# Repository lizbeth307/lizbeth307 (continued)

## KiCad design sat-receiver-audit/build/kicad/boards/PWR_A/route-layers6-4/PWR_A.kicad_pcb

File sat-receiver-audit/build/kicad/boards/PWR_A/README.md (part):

# PWR-A: розміщення і пробне розведення (W2 PCB-PWRA-1, PCB-PWRA-2, PCB-PWRA-3, PCB-PWRA-4)

**Статус: MODEL, NOT FOR FABRICATION.** Тут немає плати PWR-A, розведення чи файлів виробництва. Є специфікація-планувальник двобічної PWR-A SHRINK-2 з усіма 280 позиціями, заякореними силовими каскадами і скриптовою міддю (частина 2 W2 PCB-PWRA-3), розрахунок розміщення і пробні плати з прогонів CI: плата-скелет чернетки у `skeleton-probe/` (24 якорі графа, заглушка стику B2B2 і скриптова мідь, проба 4) і проба розміщення SHRINK-2 у `placement-probe/` (235 позицій у стані `pending`, проба 7). Це записи; вони відповідають графу до GR-5A. Результати нижче — розрахунок планувальника `pcb/board_gen.py` на стандартній бібліотеці та вимір CI на пробних платах. Вони не є результатом CI-збірки плати й не є апаратним PASS. Усі стендові ворота (тепловий контакт, струм і нагрів, бюджет опору E1-05) лишаються OPEN.

**Стан лінії після рішення про площу (11.11.2026).** F2 піднято вимірюванням: у W2 PCB-PWRA-1 заповнення всіма позиціями 0.959, планувальник розмістив 160 з 256 позицій, а варіанти F2a, F2b і обидва разом дали 0.783, 0.915 і 0.740 проти порога 0.60 (розділ «Результат»). Відповідь на F2 — SHRINK-2 (рядки W2 AREA-2 у build/15). Корпус і пара PWR-A/PWR-B на стику Samtec LSHM-150 лишаються. PWR-A звільняє місце меншим вмістом: SMD-перетворювачі TI замість модулів Pololu, SMD-запобіжники F103/F201, нижчі демпфери й дроселі, другий бік плати, правило H-TRIM і злиті роз'єми PWR-B. Цю лінію продовжують W2 PCB-PWRA-3 (виправлення `placement_study.py`, двобічна специфікація, скриптова мідь) і W2 PCB-PWRA-4 (розведення до DRC 0 і набір виробництва). Частина 1 W2 PCB-PWRA-3 (12.11.2026) виправила `placement_study.py`, перерахувала чернетку і перенесла будівник SHRINK-2 у `make_spec.py`; розрахунок і проби — розділи «Двобічна PWR-A SHRINK-2» і «Проба розміщення». Частина 2 (12.11.2026, після злиття GR-5A, GR-5B і MECH-7 у wip/w2-shrink d45870ca) перегенерувала специфікацію на реальних деталях, заякорила силові каскади й додала скриптову мідь — розділ «Частина 2: реальні деталі, силові каскади, скриптова мідь». Мету W2 PCB-PWRA-2 (розведення всіх позицій до DRC 0, перевірка THT і B2B на повній платі, набір виробництва) SHRINK-2 замінив. Пакет закрито пробами 2–4 (розділ «Пробна плата-скелет»), без нового розміщення чи розведення.

**Стан після W2 PCB-PWRA-4 (12.11.2026): F2-C спрацював.** Плату SHRINK-2 з усіма 280 позиціями дві ітерації розміщення розводили в CI (`sr-rx-pcb`, KiCad 10.0.7, Freerouting 2.5.0). Ітерація 1 лишила 220 нез'єднань і 70 помилок DRC, ітерація 2 — 198 нез'єднань і 11 помилок; кола лишилися нерозведеними після двох ітерацій розміщення, тож за брифом і тригером F2-C рішення SHRINK-2 пакет зупинився й підняв F2-C з числами (розділ «Розведення W2 PCB-PWRA-4»). Плати запису, набору виробництва і `pcb/boards/PWR_A.json` немає; виходи обох прогонів лежать як записи в `route-iteration-1/` і `route-iteration-2/`. Усе — CI/MODEL, не апаратний PASS; стендові ворота лишаються OPEN.

## Файли

| Файл | Що це |
|---|---|
| `PWR_A.spec-draft.json` | Чернетка специфікації плати за схемою `srrx-board-spec-v1`. Містить усі 256 позицій доменів PWR_MAIN, PWR_BRANCH і USB_POWER (`pcb/generated/partition.json`), тотожну мапу позицій і кіл, 4 шари, якорі, групи розміщення, таблицю вільних прямокутників `regions`, резерв під B2B, скриптову мідь, заливки після розведення та політику DRC. |
| `PWR_A.kicad_pro` | Проєкт KiCad 10.0.7: переглянуті рівні серйозності DRC (як в ENC) і класи кіл із `pcb/generated/netclasses.json`. Default/SIG має 0.15 мм, PWR1A — 0.35, PWR2A — 0.8, PWR3A — 1.85, BATT — 3.2 мм; зазор усіх класів 0.15 мм, переходи 0.6/0.3 мм. Шаблони кіл узято з `netclasses.json`, лише 48 кіл цієї плати. Мінімальний наскрізний отвір — 0.2 мм, бо футпринт LT3045 з бібліотеки KiCad (MSOP-12-1EP ThermalVias) свердлить 0.2 мм; підлога JLC для 4 шарів — 0.15 мм. |
| `placement_study.py` | Розрахунок, лише стандартна бібліотека. Він бере з `pcb/board_gen.py` перевірку специфікації, розв'язання кіл, геометрію футпринтів і полицевий пакувальник; нічого з цього не переписано. Рахує специфікацію SHRINK-2 (`SPECS`) → `placement-study-shrink2.json`; режим `--check` перевіряє відтворення. З W2 PCB-PWRA-3: виправлення перешкод, групи нижнього боку, заплановані футпринти, перевірка b2b з графовим партнером J209, H-TRIM, незалежна перевірка перекриттів `placement_checks`. Частина 2 додала: перевірку курт'ярдів низу в кишенях PB1–PB13, зон перетворювачів (`converter_zones`), кінця нижнього ряду роз'ємів (`bottom_row`), наскрізні переходи як перешкоди низу, вільну смугу праворуч від частини групи (`<область>>`), зону-заборону скриптової міді (вид `copper`, не попит площі) і перевірку скриптової міді (ширини, площадки, зазори між заливками, переходи). Виправлення огляду (F1/F2): перевірка магістралей (`scripted_copper_precheck.trunks`: скриптова мідь кожного силового кола сама з'єднує свої площадки), заливки на внутрішньому шарі (In2) і звіт коридорів (`corridor_precheck`, растр 0.2 мм: чи досягає мідь ширини класу F.Cu/B.Cu площадок, які лишено роутеру). |
| `placement-study.json` | Застиглий запис (частина 1): розрахунок чернетки з виправленням перешкод на графі wip/w2-shrink 59c68774 (166 з 257). Після GR-5A чернетка з графом не розв'язується (U107/U108 — перетворювачі TI, C107.1 — E1_CONV_IN), тож `--check` її не перевіряє; `--spec PWR_A.spec-draft.json` рахує її лише на дереві до GR-5A. |
| `placement-study-shrink2.json` | Згенерований результат (§2): не редагувати вручну, а перезапустити `python3 build/kicad/boards/PWR_A/placement_study.py`. |
| `make_spec.py` | Генератор специфікації SHRINK-2 (W2 PCB-PWRA-3, стандартна бібліотека), перенесений у репозиторій скретч-будівник рішення SHRINK-2. Читає чернетку, граф, `pcb/partition-spec.json` candidates.shrink2, стан запланованих змін (з частини 2 — наживо за правилом `pcb/partition_budget.py` Evaluator.planned, бо `pcb/partition-budget.json` старший за граф до AREA-2b), J209 з `pcb/boards/PWR_B.json`, карту контактів `pcb/generated/b2b-nets.json` і контракт MECH-7 (зони 3'/4', кишені PB1–PB13, `row_end_max`); дизайн не змінює. Пише `PWR_A.spec-shrink2.json`; `--check` перевіряє відтворення. |
| `PWR_A.spec-shrink2.json` | Згенерована (§2) специфікація-планувальник двобічної PWR-A SHRINK-2: 280 позицій, 48 якорів (силові каскади з вузлами SYS12 і LAB5, роз'єми, J208, регулятори зон 1–2), групи верху й низу, області `regions.rects` і `regions.bottom_rects` (кишені), скриптова мідь `pre_route` (55 зон: 46 на F.Cu, 4 на B.Cu, 3 на In2.Cu і 2 площини GND In1/In2; 64 переходи, 1 доріжка). Лежить тут, а не в `pcb/boards/`: плату запису (розведення до DRC 0, набір виробництва) робить W2 PCB-PWRA-4. |
| `make_probe_spec.py` | Генератор специфікацій проб (стандартна бібліотека). Скелет SHRINK-2 (частина 2): позиції з якорями (силові каскади, роз'єми, J208, регулятори зон 1–2), уся скриптова мідь (зони, переходи, доріжка), заливки після розведення, яких досягає площадка або перехід їхнього кола, і запропоновані кишені пластини для кожного скупчення THT-площадок → `skeleton-probe-shrink2/probe-spec.json`. Проба розміщення з `PWR_A.spec-shrink2.json` і `placement-study-shrink2.json`: кожна розміщена позиція на своєму місці, боці й куті → `placement-probe-shrink2/probe-spec.json`. `--install skeleton\|placement` копіює вибрану в `pcb/boards/PWR_A.json` лише для коміту проби; `--check` перевіряє обидві. Скелет чернетки (`skeleton-probe/`) — застиглий запис, `--draft-skeleton` будує його лише на дереві до GR-5A. |
| `lab5_budget.py`, `lab5-budget.json` | Модель опору міді LAB5 E1→E2 проти E1-05 (≤10 мОм; CC-36 п. 12), стандартна бібліотека. З W2 PCB-PWRA-3 бере якорі `PWR_A.spec-shrink2.json` і пару стику J208/J209 (LSHM-150); з частини 2 кінець E1 — L101.2, а скриптові заливки E1_LAB5_RAW і E1_LAB5_FUSED дають верхню межу міді перед E1-05. `lab5-budget.json` згенеровано (§2): MODEL з геометрії, не вимір. |
| `skeleton-probe/` | Застиглий запис: вихід прогону маршрутизації в CI для проби 4 чернетки (run 42424937979): 24 якорі графа, заглушка B2B2 і скриптова мідь, плюс локальний огляд `check_boards`. Згенеровано, не редагувати; див. розділ нижче. |
| `placement-probe/` | Застиглий запис: вихід прогону маршрутизації в CI для проби 7 (частина 1, стан `pending`) з її специфікацією і локальний огляд `check_boards`. Згенеровано, не редагувати; див. розділ «Проба розміщення». |
| `skeleton-probe-shrink2/`, `placement-probe-shrink2/` | Згенеровані (§2) специфікації проб частини 2 (`probe-spec.json`): скелет SHRINK-2 (48 якорів і вся скриптова мідь) і повна проба розміщення (280 позицій). Прогону CI ще не було: див. «Проби частини 2 у CI». |
| `make_board.py` | Генератор специфікації плати для розведення (W2 PCB-PWRA-4, стандартна бібліотека): будує пробу розміщення PCB-PWRA-3 (усі 280 позицій на місцях), бере позиції `board-placement.json`, переводить скриптові заливки F.Cu/B.Cu у заблоковані доріжки зі стиками (`board_copper`) і перевіряє, що мідь кожного кола — один шматок, ставить перехід GND до площин біля кожної SMD-площадки GND (`gnd_fanout`, порт PWR_B), пише висоти й зони висот (вікна PWR-B, H-TRIM), `neck_exempt` для стрижнів на виводах, класи проєкту (SCRIPTED_GND, переходи 0.7/0.3). Пише `board-spec.json` і `PWR_A.kicad_pro`; `--install` копіює специфікацію в `pcb/boards/PWR_A.json` для коміту прогону; `--check`. |
| `board-spec.json` | Згенерована (§2) специфікація плати: стан генератора після ітерації 2 (виправлення ще не розведено). |
| `place_board.py`, `board-placement.json` | Перерозміщення з урахуванням кіл (W2 PCB-PWRA-4, стандартна бібліотека): 201 позиція, що не є якорем специфікації SHRINK-2 і не має вирізу PWR-B, переходить на законні місця (контур, отвори, скриптова мідь і переходи, переходи GND нерухомих деталей, зони H-TRIM для деталей вищих за 2.7 мм, кишені пластини для нижніх чіпів), далі відпал із фіксованим зерном за половиною периметра кіл без GND із вагою класу. `board-placement.json` згенеровано (§2); `--check`. |
| `board_audit.py`, `board-audit.json` | Аудити PWR-A, яких немає в `check_boards` (W2 PCB-PWRA-4, стандартна бібліотека): зони 1–2 і 3'/4', нижні курт'ярди в кишенях PB1–PB13, H-TRIM, отвори без кола, кола E1_CELL0/B-, модель міді LAB5, E1_LAB5_RAW і E1_LAB5_FUSED, заповнення. Без плати в теці рахує заплановану плату `board-spec.json`; з `--dir` теки запису — розведену, а `--review` пише туди `review.json` `check_boards`. |
| `route-iteration-1/`, `route-iteration-2/` | Записи двох прогонів розведення W2 PCB-PWRA-4 (згенеровано, не редагувати): плата, `report.json`, `drc.json`, `connectors.json`, `route-log.json` з артефакту pcb-regenerated-PWR_A, `board-spec.json` (специфікація прогону), `review.json` і `board-audit.json` (локально). |
| `freeze/`, `route-frozen-6l.json` | Заморожене розведення 6-шарової проби W2 PWRJ-LAYERS6: копії інструментів PWR_B (`model.py`, `router.py`, `fin.py` з додатками `connect_all`, `neck_link`, `branch_pass`) і драйвер `freeze6.py` (numpy, офлайн, CI його не запускає); `route-frozen-6l.json` — мідь прогону 43349395168 (храповик 43339007739) з добудовою, шийками й гілками; `make_board.py` бере її лише при збігу захисту. |
| `route-layers6-3/` | Запис прогону 43354942122 проби W2 PWRJ-LAYERS6 (згенеровано, не редагувати): плата, `report.json`, `drc.json`, `connectors.json`, `route-log.json`, специфікація прогону, локальні `review.json` і `board-audit.json`. |

Специфікація навмисно лежить тут, а не в `pcb/boards/PWR_A.json`: специфікація в `pcb/boards/` без розведеної плати, що проходить перевірку, зробила б `sr-rx-pcb` червоним для всієї лінії інтеграції. Чернетка лишається записом до SHRINK-2. Специфікація SHRINK-2 з частини 2 має всі позиції домену (аудит домену пройдено, 280 позицій) і стає входом W2 PCB-PWRA-4, яка розводить плату запису і переносить її в `pcb/boards/PWR_A.json`. W2 PCB-PWRA-4 тримає так само і специфікацію плати: `make_board.py` пише `board-spec.json`, а в `pcb/boards/PWR_A.json` вона стоїть лише на коміт прогону (`--install`) або коли плата пройде.

## Шість шарів і 2 oz зовні (W2 PWRJ-LAYERS6, проба, CI/MODEL)

**Стан проби (13.11.2026, гілка wip/w2-pwrj-layers6): DRC 3 помилки, 64 нез'єднання, `ignored_checks` [] (sr-rx-pcb 43354942122).** Це вимір CI, не апаратний PASS; стендові ворота лишаються OPEN. Розміщення SHRINK-2 і оболонка не змінені: проба дає обом силовим платам 6 шарів.

**Шари.** S-G-S-S-P-S за таблицею JLC06161H-2116 (як PWR_B і 6-шаровий CTRL), замовлення з готовою міддю 2 oz зовні і 0.5 oz усередині (`pcb/generated/stackup-6l.json` `copper_options.outer_2oz`; jlcpcb.com/impedance, capabilities/pcb-capabilities і 6-layer-pcb прочитано 13.11.2026). In1.Cu — суцільна GND; In2.Cu і In3.Cu — лише сигнали; In4.Cu — заливка GND зі скриптовими заливками E1_CONV_IN (роль L3 4-шарового плану). Силові класи йдуть тільки по F.Cu/B.Cu (`router.class_layers`) і мають ширини для 2 oz за тим самим правилом IPC-2221 (MODEL): PWR1A 0.2, PWR2A 0.4, PWR3A 0.95, BATT 1.6 мм. Підлога JLC для 2 oz — 0.15/0.15 мм, рівно правило проєкту 0.15/0.15, тож запасу над підлогою зовні немає.

**Інструменти.** `freeze/` — копії `model.py`, `router.py`, `fin.py` з PWR_B і драйвер `freeze6.py`: заморожена мідь прогону плюс добудова сіткою A*. Добавки цієї проби: з'єднання пара за парою (`connect_all`), короткі шийки на виводах до 3 мм (`neck_link`, записуються в `neck_exempt`) і малострумові гілки до тестових точок, конденсаторів і резисторів від 100 Ом (`branch_pass`, 0.25/0.4 мм до 12 мм, записуються в `branch_exempt`); `--prev` збирає заморожену мідь попереднього файлу ще раз (храповик). `make_board.py` бере `route-frozen-6l.json` лише при збігу захисту (SHA256 площадок і скриптової міді). Режим FREEZE_ONLY вимикає автороутинг для прогону з замороженою міддю.

| Прогін | Що | DRC помилок | Нез'єднань |
|---|---|---|---|
| 43287918183 / 43295500516 | 4 шари, 1 oz (W2 PCB-PWRA-4) | 70 / 11 | 220 / 198 |
| 43339007739 | 6 шарів, 2 oz, Freerouting з нуля (222 → 191 нерозведених за його лічильником) | 1 | 138 |
| 43349395168 | заморожена мідь 43339007739 + добудова A* (10 шийок, 8 гілок), далі Freerouting | 9 | 64 |
| 43354942122 | храповик 43349395168 без 4 конфліктних шматків, автороутинг вимкнено | 3 | 64 |

Запис останнього прогону — `route-layers6-3/` (плата, звіт, DRC, журнал, специфікація прогону, локальні `review.json` і `board-audit.json`). `check_boards`: 0 знахідок (class_widths 0 на 2559 шматках, heights 0), 168 неперевірених (112 висот нижніх чіпів і роз'ємів, 35 гілок і шийок, 21 геометрія). `board_audit.py`: NO_FINDINGS, H-TRIM пройдено, бо J201 PWR-B стоїть у колонці між C219 і L102 (розміщення wip/w2-pwrbr-place). Три помилки DRC: перехід E2_AUX_SWITCHED замороженої міді на 0.1-мм стрижні LAB5, який board_gen щоразу додає до центру скриптового переходу (`via_centre_stubs`); `connection_width` на J208.1 (3V3_Q6A); 0.13-мм відгалуження E2_BONI_EF без з'єднання. Усі три — дефекти зібраної міді, не ємності.

**Чому не сходиться (MODEL, растр 0.1 мм на платі 43339007739).** Із 138 нез'єднань 104 — силові класи. Частка плати, де вміщається центр доріжки 1.6 мм (BATT), — 0.23 на F.Cu і 0.49 на B.Cu лише від нерухомої міді (площадки двобічного монтажу, скриптова мідь, 260 заблокованих переходів, зони зв'язку з пластиною), 0.16 і 0.36 після розведення; для доріжки 0.15 мм — 0.55 і 0.76 (F/B) проти 0.86 на In2/In3. Новий перехід можна поставити лише на 0.37 плати (0.21 після розведення). Внутрішні шари знімають сигнали з F/B, але силова мідь мусить лишатися на F/B, а площадки силових кіл на верху стоять у розміщенні із заповненням 0.595. Добудова A* не знаходить шляху ширини класу між острівцями цих кіл; залишок після прогону 43354942122 — 51 силове нез'єднання (BATT 25, PWR3A 17, PWR2A 4, PWR1A 5) і 13 сигнальних із 64.

**Мідь LAB5 (MODEL, 20 °C, 2 oz).** Шлях A L101.2 → L205.1 — 11.52 мОм; шлях B L101.2 → J208 — 17.84 мОм, плюс LSHM ≤ 3.75 і мідь PWR-B 3.58 / 4.57 мОм (до U210.1 / U221.1) — разом 25.2 / 26.2 мОм проти 10 мОм E1-05. 2 oz половинить мідь, але шлях B вагою міді не виконати: лише дельта стику лишає 6.25 мОм на мідь обох плат.

## Розведення W2 PCB-PWRA-4 (CI/MODEL): дві ітерації і F2-C

Мета брифу — плата запису: DRC 0 помилок і 0 нез'єднань, `review.json` без знахідок, набір виробництва з CPL обох боків, мідь LAB5 як MODEL. Кожен прогін — коміт із `[pcb-route PWR_A]` у заголовку і `pcb/boards/PWR_A.json` з `make_board.py`; бюджет Freerouting — 32 хв (вкладається в завдання плати 45 хв з DRC і аудитами).

**Рішення проєктування (обидві ітерації).**

- **GND.** Кожна SMD-площадка GND, яку не з'єднує скриптова заливка GND, має заблокований перехід 0.7/0.3 до площин In1/In2 зі стрижнем 0.25 мм (`gnd_fanout`, порт з PWR_B; довгий стрижень за растровим пошуком для нижніх чіпів під заливками верху). Клас SCRIPTED_GND роутер не розводить (`-inc`). Нез'єднань GND в обох ітераціях — 0 (у пробі 7 було 140).
- **Переходи роутера** 0.7/0.3: переходи 0.6 на зазорі 0.15 порушують правило 0.5 мм між отворами (як на PWR_B).
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
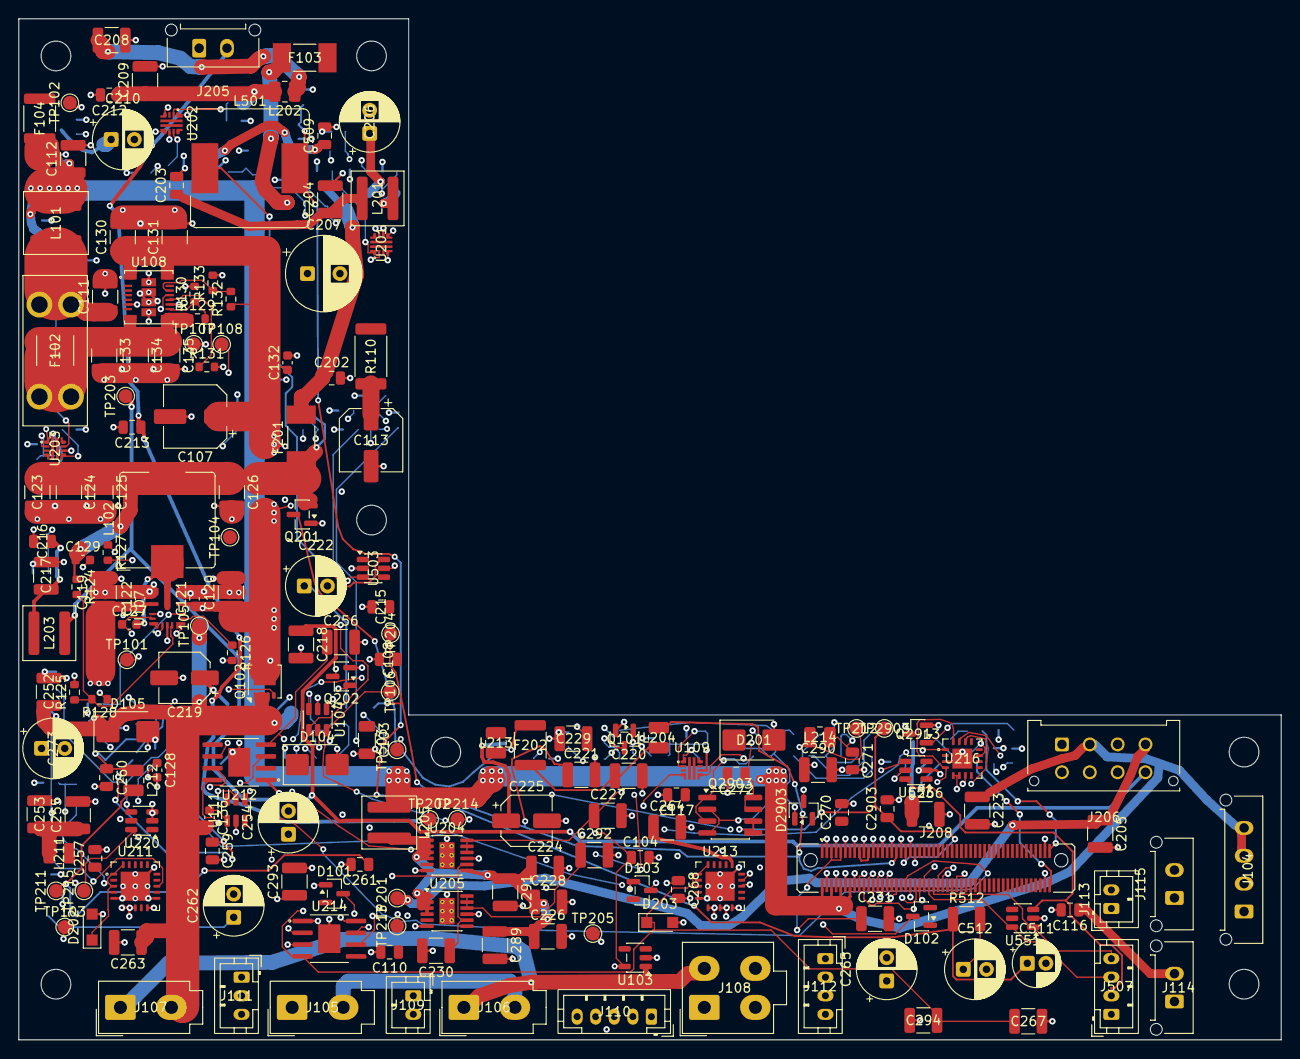
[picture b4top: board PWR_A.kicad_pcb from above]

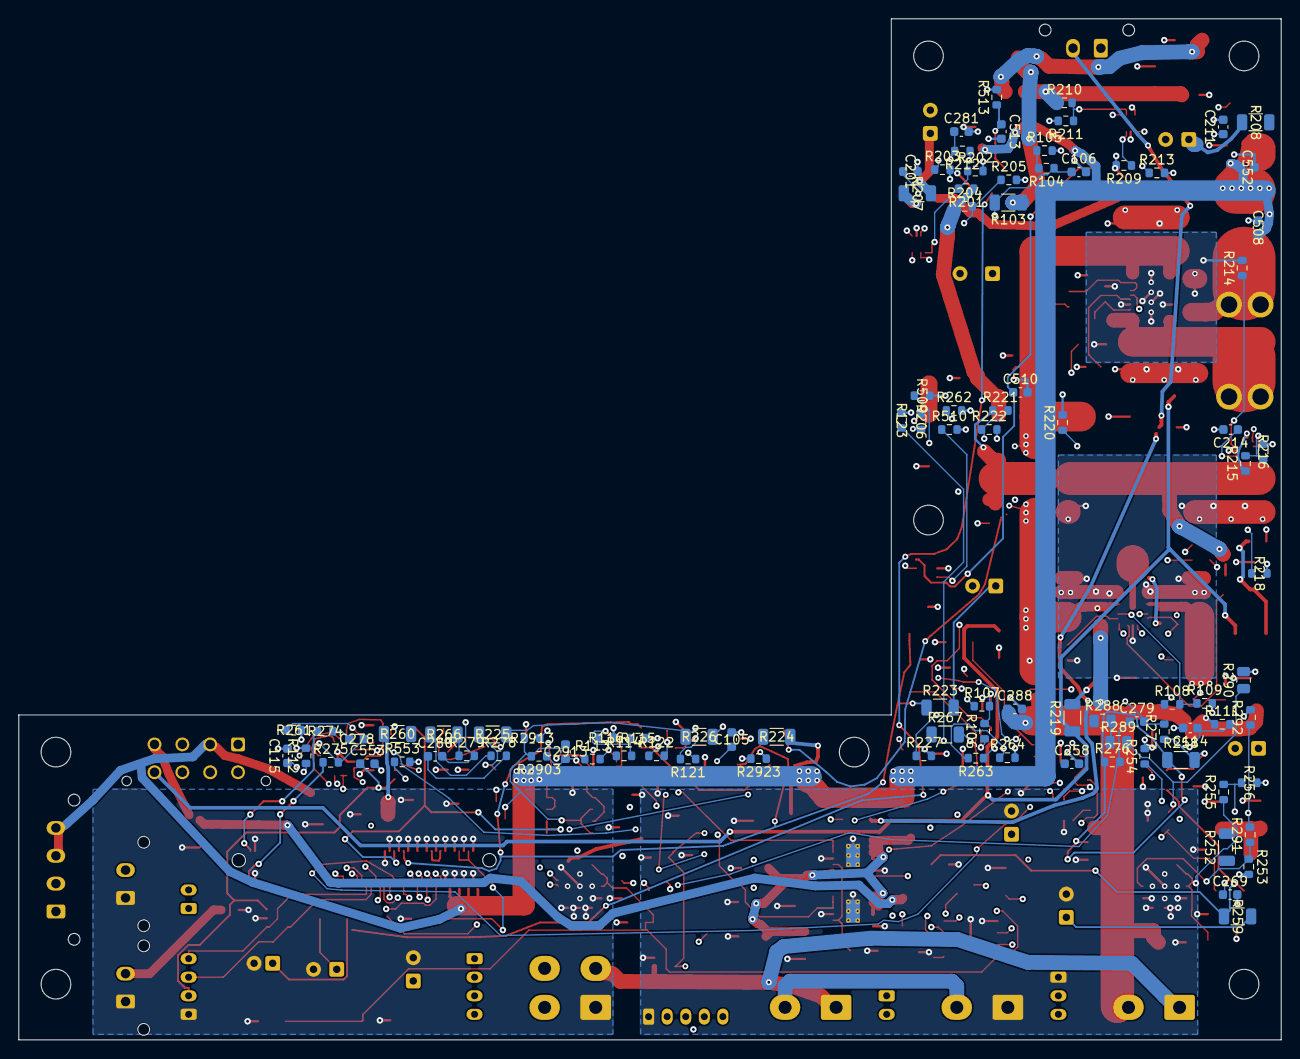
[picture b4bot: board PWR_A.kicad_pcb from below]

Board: 6 copper layers, 136.0 x 110.0 mm, 287 parts (94 on the bottom side), 148 nets.

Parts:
C103: 2.2µF50VX7R (effective≥1µF); C_1206_3216Metric
C104: 4.7µF10VX7R (effective≥2.2µF); C_0805_2012Metric
C105, C106: 100nF10VX7R; C_0603_1608Metric
C107: 100µF35VlowESR; CP_Elec_6.3x7.7
C108, C110, C116, C117: 1µF50VX7R; C_0805_2012Metric
C111, C112, C123, C124, C125, C126: 22µF50VX7R 1210 C3225X7R1H226M250AC; C_1210_3225Metric
C113: 16SVPC100M 100 µF 16 V ±20% OS-CON; CP_Elec_6.3x5.9
C114: 100nF10V; C_0603_1608Metric
C115: 3.3nF50VC0G; C_0603_1608Metric
C119, C120, C130, C131: 10µF50VX7R 1210; C_1210_3225Metric
C121, C122, C132: 100nF50VX7R; C_0603_1608Metric
C127: 100nF50VX7R CBOOT; C_0603_1608Metric
C128: 1µF16VX7R CVCC; C_0603_1608Metric
C129: 4.7pF50VC0G CFF; C_0603_1608Metric
C133, C134, C135: 47µF10VX7R 1210; C_1210_3225Metric
C136: 100nF50VX7R VCAP; C_0603_1608Metric
C201, C211, C214: 3.3nF 50V C0G C1608C0G1H332J080AA; C_0603_1608Metric
C202, C203, C212, C213, C215, C216, C257, C259, C260, C261, C268, C270, C271, C272, C2903: 1uF 50V X7R C2012X7R1H105K125AB; C_0805_2012Metric
C204, C205, C208, C209, C217, C218, C220, C221, C226, C228, C230, C252, C253, C255, C263, C264, C266, C289, C291: 10uF 50V X7R C3225X7R1H106K250AC; C_1210_3225Metric
C206, C210, C222, C254, C262, C265, C273: 47uF 50V EEUFR1H470; CP_Radial_D6.3mm_P2.50mm
C207: 220uF/25V UHE1E221MPD; CP_Radial_D8.0mm_P3.50mm
C219, C225: 47uF 10V 16SVPG47M; CP_Elec_5x4.5
C223, C224, C227, C229, C231, C256, C267, C290, C292, C293, C294: 22uF 50V X7R C3225X7R1H226M250AC; C_1210_3225Metric
C258: 47nF 50V X7R C1608X7R1H473K080AA; C_0603_1608Metric
C269, C278, C279, C280, C281, C288, C2913: 100nF 50V X7R C1608X7R1H104K080AA; C_0603_1608Metric
C508, C513, C552: 100nF X7R 10V; C_0603_1608Metric
C509: 4.7uF X7R 10V; C_0805_2012Metric
C510, C553: 1uF X7R 10V; C_0603_1608Metric
C511: EEU-FR1C101 100uF 16V; CP_Radial_D5.0mm_P2.00mm
C512: 220uF 16V low-ESR; CP_Radial_D6.3mm_P2.50mm
D101, D102, D103: BAT54,215; SOT-23
D104, D105: SMBJ17A-E3/52; D_SMB_KA
D201: SMBJ13A-E3/52; D_SMB_KA
D202, D203: PMEG4030ER; Nexperia_CFP3_SOD-123W
D2903: BZX84C10-7-F; SOT-23
F102: 4 A DC ≥32 V LAB5; Fuseholder_Blade_Mini_Keystone_3568
F103: 5A DC≥32V service SMD 0451005.MRL; Fuse_Littelfuse-NANO2-451_453
F104, F202: MF-MSMF075/24-2 0.75A; Fuse_1812_4532Metric
F201: Littelfuse 0451004.MRL 4A; Fuse_Littelfuse-NANO2-451_453
H1, H2, H3, H4, H5, H6, H7: NPTH_3.2mm
J104: X02P1-PWR: Molex Micro-Fit 3.0 4, верхній вхід, S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; Molex_Micro-Fit_3.0_43650-0415_1x04_P3.00mm_Vertical
J105: X05J1-PWR: Molex Mini-Fit Jr. 2×1, верхній вхід, 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; Molex_Mini-Fit_Jr_5566-02A_2x01_P4.20mm_Vertical
J106: X06J1-PWR: Molex Mini-Fit Jr. 2×1, верхній вхід, 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; Molex_Mini-Fit_Jr_5566-02A_2x01_P4.20mm_Vertical
J107: X07J1-PWR: Molex Mini-Fit Jr. 2×1, верхній вхід, 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; Molex_Mini-Fit_Jr_5566-02A_2x01_P4.20mm_Vertical
J108: X10J1-PWR: Molex Mini-Fit Jr. 2×2, верхній вхід, 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; Molex_Mini-Fit_Jr_5566-04A_2x02_P4.20mm_Vertical
J109: X05S1-PWR: JST PH 2, верхній вхід, S05; JST_PH_B2B-PH-K_1x02_P2.00mm_Vertical
J110: X06S1-PWR: JST PH 5, верхній вхід, S06; JST_PH_B5B-PH-K_1x05_P2.00mm_Vertical
J111: X07S1-PWR: JST PH 3, верхній вхід, S07; JST_PH_B3B-PH-K_1x03_P2.00mm_Vertical
J112: X10S1-PWR: JST PH 4, верхній вхід, S10; JST_PH_B4B-PH-K_1x04_P2.00mm_Vertical
J113: X11S1-PWR: JST PH 2, верхній вхід, S11; JST_PH_B2B-PH-K_1x02_P2.00mm_Vertical
J114: X11P1-PWR: Molex Micro-Fit 3.0 2, верхній вхід, S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; Molex_Micro-Fit_3.0_43650-0215_1x02_P3.00mm_Vertical
J115: X12P1-PWR: Molex Micro-Fit 3.0 2, верхній вхід, S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; Molex_Micro-Fit_3.0_43650-0215_1x02_P3.00mm_Vertical
J205: X19P1-PWR: Molex Micro-Fit 3.0 2, верхній вхід, S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; Molex_Micro-Fit_3.0_43650-0215_1x02_P3.00mm_Vertical
J206: SL2-PWR-MF: Molex Micro-Fit 3.0 2×4, верхній вхід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; Molex_Micro-Fit_3.0_43045-0812_2x04_P3.00mm_Vertical
J208: B2B-PWRA: Samtec LSHM-150 2×50, PWR-A верх, стик 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; Samtec_LSHM-150-xx.x-x-DV-N_2x50_P0.50mm_Vertical
J507: X32S1-PWR: JST PH 4, верхній вхід, S32; JST_PH_B4B-PH-K_1x04_P2.00mm_Vertical
L101: XAL6060-103MEC 10 µH ±20%; L_Coilcraft_XAL6060-XXX
L102: SRP1040VA-4R7M 4.7 µH ±20%; L_Bourns_SRP1038C_10.0x10.0mm
L201, L203, L205: 1uH XAL5030-102MEC; L_Coilcraft_XAL5030-XXX
L202, L204, L211, L212, L213, L214: 1uH SRP2510PA-1R0M; L_1008_2520Metric
L501: SRR1260-101M 100uH; L_Bourns_SRR1260
Q101: 2N7002,215; SOT-23
Q102: DMT6007LFG-7; Diodes_PowerDI3333-8
Q201: AO3407A; SOT-23
Q202, Q2913: 2N7002; SOT-23
Q2903: DMP6050SSD-13; SOIC-8_3.9x4.9mm_P1.27mm
R103: 3.30M0.1%25ppm; R_1206_3216Metric
R104: 332k0.1%25ppm; R_0603_1608Metric
R105: 4.02k0.1%25ppm TRIM; R_0603_1608Metric
R106, R111, R123, R124: 100k1%; R_0603_1608Metric
R107: 4.22M1%; R_0603_1608Metric
R108, R132: 1.00M1%; R_0603_1608Metric
R109: 115k1%; R_0603_1608Metric
R110: WSL2512R3300FEA 0.330 Ω 1%; R_2512_6332Metric
R112: 20.0k1%; R_0603_1608Metric
R113: 470k1%; R_0603_1608Metric
R114: 174k0.1%; R_0603_1608Metric
R115: 10.0k0.1%; R_0603_1608Metric
R116: 953Ω1%; R_0603_1608Metric
R121: 2.20k1%; R_0603_1608Metric
R122: 1.00k1%; R_0603_1608Metric
R125: 9.09k0.1%; R_0603_1608Metric
R126, R131: 14.3k1%; R_0603_1608Metric
R127: 100Ω1% RBOOT; R_0603_1608Metric
R128: 1.00k1% RFF; R_0603_1608Metric
R129: 40.2k1%; R_0603_1608Metric
R130: 10.0k1%; R_0603_1608Metric
R133: 147k1%; R_0603_1608Metric
R201, R213, R218, R220, R253, R261, R292, R2903: 100k 1%; R_0603_1608Metric
R202: 13.0k 1% 100ppm; R_0603_1608Metric
R203: 825R 1%; R_0603_1608Metric
R204, R210: 102k 0.1%; R_0603_1608Metric
R205, R211, R216: 10.0k 0.1%; R_0603_1608Metric
R206, R212, R221, R222, R2923: 10.0k 1%; R_0603_1608Metric
R207, R208, R223, R252, R259, R260, R267: 0.22R 1% 0.25W; R_1206_3216Metric
R209: 1.96k 1%; R_0603_1608Metric
R214: 1.65k 1%; R_0603_1608Metric
R215: 19.6k 0.1%; R_0603_1608Metric
R219, R224: 0.15R 1% 0.25W; R_1206_3216Metric
R225, R226: 20mR 1% 0.25W; R_1206_3216Metric
R227: 21.5k 0.1% 25ppm; R_0603_1608Metric
R254: 2.05k 1%; R_0603_1608Metric
R255: 110k 0.5%; R_0603_1608Metric
R256: 10.0k 0.5%; R_0603_1608Metric
R258: 0.100R 0.1% 0.25W Kelvin; R_1206_3216Metric
R262: 7.15k 1% 100ppm; R_0603_1608Metric
R263: OVLO TBD (start 102k 0.1%); R_0603_1608Metric
R264: OVLO TBD (start 9.09k 0.1%); R_0603_1608Metric
R266: 0.200R 0.1% 0.25W Kelvin; R_1206_3216Metric
R274, R275, R276, R277, R278, R279: 10.0R 1%; R_0603_1608Metric
R288: TNPW0805332KBYEA 332k 0.1%10ppm; R_0805_2012Metric
R289: TNPW08052K00BYEA 2.00k 0.1%10ppm; R_0805_2012Metric
R290: TNPW080510K0BYEA 10.0k 0.1%10ppm; R_0805_2012Metric
R291: 4.70k 1%; R_0603_1608Metric
R509: RILIM TBD (start 28.7k 1%); R_0603_1608Metric
R510: 100k; R_0603_1608Metric
R512: 1Ohm 0.5W; R_1210_3225Metric
R513: 10k; R_0603_1608Metric
R553: RILIM TBD (start 88.7k 1%); R_0603_1608Metric
R2913: 22k 1%; R_0603_1608Metric
TP101: PG_SYS12резерв; TestPoint_Pad_D1.5mm
TP102: PG_LAB5резерв; TestPoint_Pad_D1.5mm
TP103: PD_FLT service; TestPoint_Pad_D1.5mm
TP104: ВузолN; TestPoint_Pad_D1.5mm
TP105: ВузолSW; TestPoint_Pad_D1.5mm
TP106: AON3V3; TestPoint_Pad_D1.5mm
TP107: Protectedground; TestPoint_Pad_D1.5mm
TP108: UV_OFF; TestPoint_Pad_D1.5mm
TP201: J21; TestPoint_Pad_D1.5mm
TP202: DISP12; TestPoint_Pad_D1.5mm
TP203: LIME3V3; TestPoint_Pad_D1.5mm
TP204: AUX12; TestPoint_Pad_D1.5mm
TP205: LNA4V5; TestPoint_Pad_D1.5mm
TP211: LNB13V2; TestPoint_Pad_D1.5mm
TP212: BONI13V8; TestPoint_Pad_D1.5mm
TP213: E2_FAULT_J21; TestPoint_Pad_D1.5mm
TP214: E2_FAULT_DISP; TestPoint_Pad_D1.5mm
TP215: OVP_LNB_N; TestPoint_Pad_D1.5mm
TP503: IMU 5V switch FAULT_N test point; TestPoint_Pad_D1.5mm
TP2903: BONI13V8_PORT; TestPoint_Pad_D1.5mm
U103: TPS70933DBVR; SOT-23-5
U104: MCP65R41T-1202E/CHY; SOT-23-6
U107: LM61460AANRJRR; TI_RJR0014A_VQFN-HR-14_4x3.5mm
U108: TPSM63606RDLR — LAB5 default; TI_RDL0020A_B3QFN-20_5x5.5mm
U109: TPS259470ARPWR USB-C; TI_RPW0010A_VQFN-HR-10_2x2mm_P0.5mm
U111: LM74700QDBVRQ1; SOT-23-6
U201, U202, U203: TPS259470ARPWR; TI_RPW0010A_VQFN-HR-10_2x2mm_P0.5mm
U204, U205: LT3045EMSE#PBF; MSOP-12-1EP_3x4.039mm_P0.65mm_EP1.651x2.845mm_ThermalVias
U211, U213: TPS7A4701RGWT; TI_RGW0020A_VQFN-20-1EP_5x5mm_P0.65mm_EP3.15x3.15mm
U212, U214: TPS259630DDAR; TI_DDA0008_HSOP-8-1EP_3.9x4.9mm_P1.27mm_EP2.4x3.1mm
U216: INA3221AIRGVR; TI_RGV0016A_VQFN-16-1EP_4x4mm_P0.65mm_EP2.16x2.16mm
U220: TPS3701DDCR; TSOT-23-6
U503: TPS2553DBVR-1; SOT-23-6
U551: TPD4E1U06DBVR; SOT-23-6
U553: TPS2553DBVR; SOT-23-6

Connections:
3V3_Q6A: C281.1, J208.1, R206.2, R212.2, U216.4, U216.16
AON3V3: C104.1, C105.1, J110.2, TP106.1, U103.5, U104.6
AUX12: C221.1, J208.33, L204.2, R223.1, TP204.1
AUX12_DAMP: C222.1, R223.2
BONI13V8: C272.1, J208.25, L214.2, Q2903.7, Q2903.8, R267.1, R2923.1, TP212.1
BONI13V8_DAMP: C273.1, R267.2
BONI13V8_PORT: C2903.1, J208.37, Q2903.5, Q2903.6, TP2903.1
CHG_INHIBIT: J208.18, R122.1
DISP12: C213.1, J205.2, TP202.1, U202.6
E1_BAT_ADC: C114.1, J208.20, R111.2, R112.1
E1_CHG_CC1: J112.1, J113.1
E1_CHG_CC2: J112.2, J113.2
E1_CHG_GATE: Q101.1, R122.2, R123.1
E1_CHG_INHIBIT_LOW: J112.3, Q101.3, R121.2
E1_CHG_NTC: J109.1, J112.4, R121.1
E1_CONV_IN: C107.1, C119.1, C120.1, C121.1, C122.1, C130.1, C131.1, C132.1, Q102.5, R108.1, R132.1, U107.8, U107.12, U108.1, U108.16, U111.4
E1_EN_LAB5: R132.2, R133.1, U108.14
E1_EN_SYS12: R108.2, R109.1, U107.7
E1_LAB5_DAMP: C113.1, R110.2
E1_LAB5_FB: R129.2, R130.1, U108.10
E1_LAB5_FUSED: C111.1, F102.2, L101.1
E1_LAB5_RAW: C133.1, C134.1, C135.1, F102.1, R129.1, U108.5, U108.8, U108.9
E1_LAB5_RT: R131.1, U108.12
E1_MASTER_OFF: D101.3, D102.3, J111.2
E1_N: C103.1, D104.K, F103.1, J106.1, J107.1, J108.2, R103.1, TP104.1, U103.1
E1_PD_DVDT: C115.1, U109.7
E1_PD_EN: R113.2, U109.1
E1_PD_FLT: TP103.1, U109.4
E1_PD_ILM: R116.1, U109.9
E1_PD_OVLO: R114.2, R115.1, U109.2
E1_PG_LAB5: TP102.1, U108.13
E1_PG_SYS12: TP101.1, U107.5
E1_RPP_GATE: Q102.4, U111.5
E1_RPP_VCAP: C136.1, U111.1
E1_SERVICE_P: F103.2, J115.2
E1_SHUNT_P: J105.2, J106.2
E1_SW: C108.1, C110.1, C136.2, C252.1, C263.1, C288.1, D105.K, J107.2, L211.1, L213.1, Q102.1, Q102.2, Q102.3, R111.1, TP105.1, U111.3, U111.6, U220.5
E1_SWITCH_A: D103.1, J111.3
E1_SYS12_CBOOT: C127.1, R127.1, U107.14
E1_SYS12_FB: R124.2, R125.1, R128.2, U107.4
E1_SYS12_FF: C129.2, R128.1
E1_SYS12_RBOOT: R127.2, U107.13
E1_SYS12_RT: R126.1, U107.6
E1_SYS12_SW: C127.2, L102.1, U107.10
E1_SYS12_VCC: C128.1, U107.2
E1_USB_PD_RAW: C116.1, J114.2, R113.1, R114.1, U109.5
E1_USB_PD_SAFE: C117.1, J108.3, U109.6
E1_UV_OFF: D101.1, R107.1, TP108.1, U104.1
E1_UV_REF: R106.1, U104.5
E1_UV_REFH: R106.2, R107.2, U104.3
E1_UV_SENSE: C106.1, R103.2, R104.1, U104.4
E1_UV_TRIM: R104.2, R105.1
E2_AUX_GATE: Q201.1, R221.2, R222.1
E2_AUX_GSINK: Q202.3, R222.2
E2_AUX_PTC: C220.1, F202.2, L204.1
E2_AUX_SWITCHED: F202.1, Q201.3
E2_BLKB_G: C2913.2, D2903.1, Q2903.2, Q2903.4, R2903.2, R2913.1
E2_BLKB_S: C2913.1, D2903.3, Q2903.1, Q2903.3, R2903.1
E2_BLKB_SINK: Q2913.3, R2913.2
E2_BONI_DVDT: C269.1, U214.2
E2_BONI_EF: C270.1, R266.1, R278.1, U214.5
E2_BONI_ILM: R262.1, U214.7
E2_BONI_IN: C264.1, C266.1, L213.2, R260.1, U213.15, U213.16
E2_BONI_IN_DAMP: C265.1, R260.2
E2_BONI_LDO: C267.1, C294.1, D203.1, R263.1, U213.1, U213.3, U213.20, U214.4
E2_BONI_MON: C271.1, L214.1, R266.2, R279.1
E2_BONI_NR: C268.1, U213.14
E2_BONI_OV: R263.2, R264.1, U214.8
E2_DISP_IN: C209.1, C212.1, L202.2, R208.1, R210.1, U202.5
E2_DISP_IN_DAMP: C210.1, R208.2
E2_FAULT_DISP: R212.1, TP214.1, U202.4
E2_FAULT_J21: R206.1, TP213.1, U201.4
E2_J21_EF: C203.1, C204.1, L201.1, U201.6
E2_J21_EN: R201.2, R202.1, U201.1
E2_J21_FUSED: C202.1, F201.2, R201.1, R204.1, U201.5
E2_LIME_EF: C216.1, C217.1, L203.1, U203.6
E2_LNA4_SHUNT: J208.100, R275.1
E2_LNA4_SW: J208.99, R274.1
E2_LNA_IN: C224.1, C226.1, C228.1, C289.1, C291.1, L205.2, R224.1, U204.1, U204.2, U204.3, U204.4, U204.7, U205.1, U205.2, U205.3, U205.4, U205.7
E2_LNA_IN_DAMP: C225.1, R224.2
E2_LNA_SET: C230.1, R227.1, U204.8, U205.8
E2_LNB_DVDT: C258.1, U212.2
E2_LNB_EF: C259.1, R258.1, R276.1, U212.5
E2_LNB_ILM: R254.1, U212.7
E2_LNB_IN: C253.1, C255.1, L211.2, R252.1, U211.15, U211.16
E2_LNB_IN_DAMP: C254.1, R252.2
E2_LNB_LDO: C256.1, C293.1, D202.1, R255.1, R288.1, U211.1, U211.3, U211.20, U212.4
E2_LNB_MON: C260.1, L212.1, R258.2, R277.1
E2_LNB_NR: C257.1, U211.14
E2_LNB_OV: R255.2, R256.1, U212.8
E2_LNB_OV_DIV_MID: R288.2, R289.1
E2_LNB_PRECISE_SENSE: R289.2, R290.1, U220.4
E2_LT_OUT1: C227.1, C290.1, R225.1, U204.10, U204.11, U204.12
E2_LT_OUT2: C229.1, C292.1, R226.1, U205.10, U205.11, U205.12
E2_U201_DVDT: C201.1, U201.7
E2_U201_ILM: R203.1, U201.9
E2_U201_OV: R204.2, R205.1, U201.2
E2_U202_DVDT: C211.1, U202.7
E2_U202_ILM: R209.1, U202.9
E2_U202_OV: R210.2, R211.1, U202.2
E2_U203_DVDT: C214.1, U203.7
E2_U203_ILM: R214.1, U203.9
E2_U203_OV: R215.2, R216.1, U203.2
E2_U216_IM1: C278.2, R275.2, U216.11
E2_U216_IM2: C279.2, R277.2, U216.14
E2_U216_IM3: C280.2, R279.2, U216.1
E2_U216_IP1: C278.1, R274.2, U216.12
E2_U216_IP2: C279.1, R276.2, U216.15
E2_U216_IP3: C280.1, R278.2, U216.2
E5_HFP_DAMP: C512.1, R512.2
E5_IMU5V: C553.1, J507.2, U551.3, U553.6
E5_IMU_FAULT: TP503.1, U553.4
E5_U503_ILIM: R509.1, U503.5
E5_U553_ILIM: R553.1, U553.5
E5_VBUS_HFP_SW: C510.1, L501.1, U503.6
EN_AUX12: J208.22, Q202.1, R220.1
EN_BONI: J208.24, Q2913.1, R261.1, U213.13, U214.3
EN_HFP: J208.26, R510.1, U503.3
EN_LIME3V3: J208.28, R218.1, U203.1
EN_LNB: J208.30, R253.1, R291.1, U211.13
FAULT_HFP: J208.32, U503.4
FLT_BONI: J208.34, U214.6
FLT_LIME3V3: J208.36, U203.4
FLT_LNB: J208.38, U212.6
GND: C103.2, C104.2, C105.2, C106.2, C107.2, C108.2, C110.2, C111.2, C112.2, C113.2, C114.2, C115.2, C116.2, C117.2, C119.2, C120.2, C121.2, C122.2, C123.2, C124.2, C125.2, C126.2, C128.2, C130.2, C131.2, C132.2, C133.2, C134.2, C135.2, C201.2, C202.2, C203.2, C204.2, C205.2, C206.2, C207.2, C208.2, C209.2, C210.2, C211.2, C212.2, C213.2, C214.2, C215.2, C216.2, C217.2, C218.2, C219.2, C220.2, C221.2, C222.2, C223.2, C224.2, C225.2, C226.2, C227.2, C228.2, C229.2, C230.2, C231.2, C252.2, C253.2, C254.2, C255.2, C256.2, C257.2, C258.2, C259.2, C260.2, C261.2, C262.2, C263.2, C264.2, C265.2, C266.2, C267.2, C268.2, C269.2, C270.2, C271.2, C272.2, C273.2, C281.2, C288.2, C289.2, C290.2, C291.2, C292.2, C293.2, C294.2, C508.2, C509.2, C510.2, C511.2, C512.2, C513.2, C552.2, C553.2, C2903.2, D104.A, D105.A, D201.A, D202.2, D203.2, J104.1, J104.2, J105.1, J108.1, J110.1, J111.1, J114.1, J115.1, J205.1, J206.1, J206.3, J206.5, J206.7, J208.3, J208.4, J208.7, J208.8, J208.11, J208.12, J208.15, J208.16, J208.19, J208.23, J208.27, J208.31, J208.35, J208.39, J208.41, J208.97, J208.98, J507.1, Q101.2, Q202.2, Q2913.2, R105.2, R109.2, R112.2, R115.2, R116.2, R123.2, R125.2, R126.2, R130.2, R131.2, R133.2, R202.2, R203.2, R205.2, R209.2, R211.2, R213.2, R214.2, R216.2, R218.2, R220.2, R227.2, R253.2, R254.2, R256.2, R261.2, R262.2, R264.2, R290.2, R292.2, R509.2, R510.2, R513.2, R553.2, R2923.2, TP107.1, U103.2, U104.2, U107.3, U107.9, U107.11, U108.6, U108.11, U108.17, U108.18, U108.19, U108.20, U109.8, U111.2, U201.8, U202.8, U203.8, U204.6, U204.9, U204.13, U205.6, U205.9, U205.13, U211.5, U211.6, U211.7, U211.8, U211.10, U211.11, U211.EP, U212.1, U212.EP, U213.5, U213.6, U213.7, U213.8, U213.9, U213.10, U213.EP, U214.1, U214.EP, U216.3, U216.EP, U220.2, U220.3, U503.2, U551.2, U553.2
I2C0_SCL: J110.3, J208.40
I2C0_SDA: J110.4, J208.42
I2C2_SCL: J208.44, U216.5, U216.6
I2C2_SDA: J208.46, U216.7
IMU_RX: J208.48, J507.3, U551.6
IMU_TX: J208.50, J507.4, U551.1
INA228_ALERT: J110.5, J208.52
J21: C205.1, C207.1, D201.K, J206.4, L201.2, R207.1, TP201.1
J21_DAMP: C206.1, R207.2
LAB5: C112.1, C223.1, C508.1, C509.1, C552.1, F104.1, J104.3, J104.4, J206.2, J208.2, J208.6, J208.10, J208.14, L101.2, L205.1, R110.1, U503.1, U553.1, U553.3
LAB5_RLY: F104.2, J208.17, J208.21
LIME3V3: C218.1, J206.8, L203.2, R219.1, TP203.1
LIME3V3_DAMP: C219.1, R219.2
LNA4V5: C231.1, J208.5, J208.9, R225.2, R226.2, TP205.1
LNB13V2: C261.1, J208.29, L212.2, R259.1, TP211.1
LNB13V2_DAMP: C262.1, R259.2
OVP_LNB_N: J208.54, R291.2, R292.1, TP215.1, U212.3, U220.6
PICO_DISP_EN: J208.56, R213.1, U202.1
PICO_OFF: D102.1, J208.58
PWR_BUTTON: D103.3, J208.60
SYS12: C123.1, C124.1, C125.1, C126.1, C129.1, C208.1, F201.1, L102.2, L202.1, Q201.2, R124.1, R221.1, U107.1
VBUS_HFP: C511.1, C513.1, J208.13, L501.2, R512.1, R513.1
VCC_3V3_MKEY: C215.1, J206.6, R215.1, U203.5

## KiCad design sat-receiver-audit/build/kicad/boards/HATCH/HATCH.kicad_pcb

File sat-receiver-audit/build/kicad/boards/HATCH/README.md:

# Плата сервісного лючка HATCH, 38 × 21.5 мм — W2 PCB-SB1

**Статус: `SB1_ROUTED_MECH_FIT_OPEN_NOT_FOR_FABRICATION`.** Плату розміщено й розведено в `sr-rx-pcb` (KiCad 10.0.7, Freerouting 2.5.0; прогін розведення 43129454692 на 00ae328 — повторне розведення на смузі wip/w2-int після злиття B2B: входи ті самі, аудит межі тепер рахує J208/J209; результат той самий, що в прогоні 42421953772 на 4ffd307): DRC — помилок 0, непідключених 0, попереджень 0, `ignored_checks` порожній; аудит source-pad — 0 помилок; аудит межі — `pass` (кожне коло, що виходить з плати, закінчується на роз'ємі графа); незалежна перевірка `pcb/check_boards.py` — 0 знахідок, висоти 5 роз'ємів перевірено проти пропозиції контракту. Це результат CI/моделі, а не випуск у виробництво й не апаратний PASS; механічне припасування лишається OPEN (нижче).

## Файли

| Файл | Що це |
|---|---|
| `../../../../pcb/boards/HATCH.json` | специфікація плати для `pcb/board_gen.py` і `pcb/check_boards.py` |
| `contract-proposal.json` | контур, отвори, зони без міді, висоти й розташування в корпусі — **пропозиція** W2 PCB-SB1 з джерелами кожного числа; у контракті механіки (`mechanical/generated/contract/boards.json`) плати HATCH ще немає |
| `HATCH.kicad_pro` | проєкт KiCad: перевірені рівні всіх перевірок DRC і правила (той самий набір, що в ENC) |
| `HATCH.kicad_pcb`, `report.json`, `drc.json`, `connectors.json`, `route-log.json`, `HATCH-top.svg`, `HATCH-bottom.svg`, `fp-lib-table` | виходи прогону `[pcb-route HATCH]` (§2: лише патчем `pcb-regenerated-HATCH` у коміті `GENERATED:`) |
| `review.json` | незалежна перевірка `pcb/check_boards.py --board HATCH` |
| `fab/` | набір файлів виробництва `pcb/fab_export.py` (власний `README.md`, NOT RELEASED) |

## Розташування й розміщення

Координати плати — мм, початок у точці корпусу (108.0, 68.5), осі паралельні осям корпусу, y угору. Плата стоїть у вікні лючка на z 11.9–13.5 (площина «плати як панелі» MECH-4); верхній бік (F) дивиться всередину корпусу, нижній (B) — у відкритий лючок.

- **Контур:** вікно x 8–30 (корпус x 116–138), y 0–21.5 (корпус y 68.5–90) і два вушка 8 × 10 (корпус x 108–116 і 138–146, y 80–90) за задньою стінкою. Смуга вікна y 40–56.5 лишається доступом до синього USB-A Q6A (R-F101-ACCESS), смуга y 56.5–68.5 — вільна.
- **Отвори:** ⌀2.7 на (4, 16.5) і (34, 16.5), тобто корпус (112, 85) і (142, 85); зона без міді ⌀8.0 (бобишка ⌀7.8 = вставка TC-M2,5x4 ⌀D1 4.6 + 2 × стінка 1.6). Кріплення — build/17 F38.
- **Бік лючка (B):** J502 B3B-PH-K (консоль UART5: GND, TX Q6A, RX Q6A) — сюди вмикають зовнішній адаптер USB-UART; з розеткою 8.0 мм при 9.4 мм до внутрішньої грані задньої стінки.
- **Внутрішній бік (F):** J503 43650-0315 (S16 до J21 Q6A: 12 V, GND, PWR_ON_KEY) і J509 43650-0215 (S14 від PWR: GND, J21) один над одним біля лінії отворів; J513 B3B-PH-K (S30: GND, RX, TX) і J510 B2B-PH-K (S15: PWR_ON_KEY, контакт 2 — резерв) нижче. Micro-Fit з розеткою стоять 17.27 мм — до задньої грані пластини (z 38.5) є 25 мм.
- **Мідь:** J21 (клас PWR3A, 2.5 A тривало / 4 A захист) — скриптова заблокована доріжка 2.0 мм на F.Cu від J509.2 до J503.1 (вимога класу 1.85 мм на одному зовнішньому шарі 1 oz); решту кіл (UART5, PWR_ON_KEY, GND) розводить Freerouting (0.25 мм, без перехідних отворів); GND — ще й заливки на обох боках.
- Усі деталі — THT; виводи виходять на обидва боки, тож деталі верхнього й нижнього боків не перекриваються в плані (`pth_inside_courtyard` — помилка DRC).

## Чому SW501 не на цій платі

MECH-4 моделював кнопку EDL SW501 (E-Switch PV6F240SS) крізь плату лючка як крізь панель. На платі ж є п'ять роз'ємів графа (J502, J503 і роз'єми джгутів W2 GR-3 J509, J510, J513; кортиярди KiCad 10.0.7 — 301 мм²). PV6.pdf (E-Switch, 28.08.2025, прочитано 07.11.2026, сторінки відрендерено PyMuPDF): безель ⌀18.00 × 1.50, рекомендований виріз ⌀16.00 +0.20/−0, панель 1–10 мм, гайку M16 × 1.0 не розмірено; резерв гайки ⌀22 × 3.5 — припущення MECH-4 (`mechanical/params/parts.json` pv6_button). Виводи THT проходять обидва боки, тож кожен роз'єм має стояти поза ⌀22 + 0.5 навколо осі кнопки. Перебір із кроком 0.5 мм по всіх позиціях PV6 у вікні 22 × 33.5 (над смугою USB-A) не знаходить розміщення п'яти роз'ємів навіть без кріплень (щонайбільше 3 з 5); лише з безелем ⌀19 без гайки деякі позиції вміщують роз'єми, але тоді немає місця для кріплень. Тому кнопку з плати знято (рішення «Плата лючка HATCH (W2 PCB-SB1)», build/15); її нове місце — механіка (OPEN). На колах це не позначається: SW501 з'єднана проводами S31 з майданчиками EDL Q6A (J522), а не з міддю плати.

## OPEN

- **Механіка:** перенести SW501 (`edl_key_body`, build/17 F34, правило R-PWR-KEY для SW501); записати HATCH у `mechanical/params/boards.json` і контракт за `contract-proposal.json` (тоді `contract.file` специфікації переходить на `mechanical/generated/contract/boards.json`, і плату один раз перерозводять з `[pcb-route HATCH]`: проєкція контракту в `board_gen.py` хешує й стек контракту, а там він 4-шаровий); дві бобишки на (112, 85) і (142, 85); конверт роз'ємів внутрішнього боку замість `edl_key_body`; перевірка зіткнень і трас S14, S15, S16, S30 до цих роз'ємів.
- **Механіка — зіткнення з INA228 після W2 MECH-5 (R-HATCH-BOARD-FIT):** гілка `wip/w2-mech5` (ed64c19f; у `wip/w2-int` її ще немає) переносить конверт INA228 5832 (`mechanical/params/mechanical.json:729-733` там, `layout.items` ina228) на box [86.0, 74.98, 5.5, 25.8, 20.32, 10.1], тобто x 86–111.8, y 74.98–95.3, z 5.5–15.6. Ліве вушко цієї плати (корпус x 108–116, y 80–90, z 11.9–13.5) і бобишка ⌀7.8 під ним (вісь (112, 85), z 2.5–11.9) заходять у цей конверт: перекриття 3.8 × 10 × 1.6 мм (вушко) і 3.7 × 7.8 × 6.4 мм (бобишка, узята квадратом 7.8) — перевірка коробок за `layout.items` 11.11.2026, результат моделі, не стенда; на розкладці `wip/w2-int` перекриттів немає. Автоматично цього ніхто не впіймає: HATCH немає в `mechanical/params/boards.json`, тож `sr-rx-mech` плату не моделює. Смуга y 64.4–74.98 ліворуч від вікна не вільна: там S06, S07 і S25 спускаються в (115.3, 74.25) із z 33 до z 10.55/9.55 і звідти на тій висоті йдуть на захід під HF+ (осьові лінії `mechanical/generated/harness-routes.json` на `wip/w2-int`); цей спуск іде за 0.7 мм від краю вікна x 116 (осьова лінія; діаметр джгутів S06/S07/S25 на `wip/w2-int` — 6.42/5.43/2.44 мм), тож і він входить у ту саму перевірку. Розв'язок — лінія механіки або INT: або перенести ліве кріплення на рамку посадки кришки над вікном чи під ним, або MECH-5 зсуває INA228 щонайменше на 3.8 мм у −x (з власною перевіркою зіткнень; праве гвинтове гніздо INA228 (109.06, 77.52), `module_mounts` ina228 там, стоїть за 8.0 мм від осі лівої бобишки); потім HATCH один раз перерозводять з `[pcb-route HATCH]`.
- **Доступ до J21 з лючка:** J503 стоїть усередину, тож S16 від'єднують лише після зняття плати (F38, на розкритому корпусі). Кутовий Micro-Fit 3.0 43650 на 3 контакти на боці лючка (розетка 6.98 мм, родина MF_ra у `mechanical/params/parts.json`) зробив би його доступним — зміна посадкового місця J503 у `design/E5.json` (лінія GR).
- **Кріплення F38:** довжина гвинта TBD — стосу HATCH-BOARD у `mechanical/generated/fastener-stacks.json` немає; дві вставки TC-M2,5x4 ще не додано до кількості AI-INSERT-M25.
- **Правила:** `pcb/rules/jlc-2l.kicad_dru` не підключено (`rules_file` має лишатися `null`, доки `board_gen.py` не копіює й не хешує `.kicad_dru`).
- Бенч: прозвонка, посадка розеток, струм J21 і нагрів доріжки — ворота стенда лишаються OPEN.

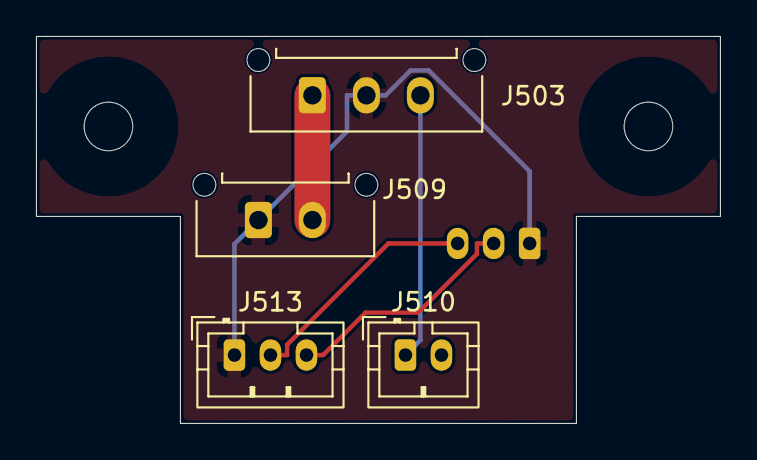
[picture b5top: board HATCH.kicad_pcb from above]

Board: 2 copper layers, 38.0 x 21.5 mm, 7 parts (1 on the bottom side), 5 nets.

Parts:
H1, H2: NPTH_2.7mm
J502: UART5 console 3pin locking; JST_PH_B3B-PH-K_1x03_P2.00mm_Vertical
J503: J21 service harness 3pin locking; Molex_Micro-Fit_3.0_43650-0315_1x03_P3.00mm_Vertical
J509: X14P1-HATCH: Molex Micro-Fit 3.0 2, верхній вхід,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; Molex_Micro-Fit_3.0_43650-0215_1x02_P3.00mm_Vertical
J510: X15S1-HATCH: JST PH 2, верхній вхід, S15; JST_PH_B2B-PH-K_1x02_P2.00mm_Vertical
J513: X30S1-HATCH: JST PH 3, верхній вхід, S30; JST_PH_B3B-PH-K_1x03_P2.00mm_Vertical

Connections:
GND: J502.1, J503.2, J509.1, J513.1
J21: J503.1, J509.2
PWR_ON_KEY: J503.3, J510.1
UART5_RX: J502.3, J513.2
UART5_TX: J502.2, J513.3

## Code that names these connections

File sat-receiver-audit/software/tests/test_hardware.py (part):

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        return hardware, bus

    def test_map_matches_named_physical_pins_and_output_only_revision(self):
        self.assertEqual(self.mapping["outputs"]["CHG_INHIBIT"], {"address": 0x23, "port": 1, "bit": 4})
        self.assertEqual(self.mapping["outputs"]["EN_LNA3"], {"address": 0x20, "port": 0, "bit": 7})
        self.assertEqual(self.mapping["inputs"]["OVP_LNB_N"], {"address": 0x23, "port": 1, "bit": 5})
        self.assertFalse(any(pin["bit"] == 7 for pin in self.mapping["inputs"].values()))

    def test_sim_starts_safe_and_does_not_invent_adc_registers(self):
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        self.assertEqual(bus.registers[0x23][OLAT + 1], 0x10)
        self.assertFalse(bus.registers[0x23][GPPU + 1] & 0x20)
        self.assertTrue(hardware.initialized)
        # Shared open-drain MCP_INT: every chip is ODR|MIRROR before any GPINTEN.
        enables = [i for i, (addr, register, data) in enumerate(bus.writes) if register == GPINTEN and any(data)]
        iocon = [i for i, (addr, register, data) in enumerate(bus.writes) if register == IOCON]
        self.assertEqual(len(iocon), len(ADDRESSES))
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        # OVP_LNB_N/PG/DCS edges must not occupy U303/U302 INTF and hide a fault pulse.
        self.assertEqual(bus.registers[0x23][GPINTEN:GPINTEN + 2], b"\x20\x0f")
        self.assertEqual(bus.registers[0x22][GPINTEN:GPINTEN + 2], b"\x7f\x00")
        ovp = self.mapping["inputs"]["OVP_LNB_N"]
        self.assertFalse(bus.registers[ovp["address"]][GPINTEN + ovp["port"]] & 1 << ovp["bit"])

    def test_non_reset_ipol_defval_or_intcon_requires_reset_without_writes(self):
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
